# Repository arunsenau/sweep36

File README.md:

# Name

sweep36

A 36 key version of the sweep, maintaining the original diodeless pcb.

# Variations

## sweeeeep

why the name sweeeeep? because an elite-c is required to support the extra features, and an elite-c has 5 additional pins... so 5 Es for the 5 extra pins. Yes, it's dumb, I know.

### Descripiton

This is a reversible pcb that is wired only, has per key leds (only on one of the two variations), oled, and choc spacing. In order to continue to support a no diode setup, I added support for the elite-c, and this is now required for the build. You can use alternative elite-c compatible controllers.

### Versions and features

There are 6 versions of this pcb, as found in the pcb/wired-rgb directory:
* choc: No hotswap, 36 keys
* choc-rotated-inner-thumb: No hotswap, 36 keys, rotated inner thumb similar to the corne
* choc-hotswap: Hotswap only, 36 keys
* ks27-choc: Support for both choc and gateron ks-27 switches, no hotswap. Note that ks-27 switches use MX keycaps on a low profile switch. Given it's choc spacing, you will likely need to use custom smaller MX keycaps if using these switches
* choc-evq-inside: No hotswap, 34 key, with an evqwgd001 roller encoder on the inside thumb key
* choc-evq-outside: No hotswap, 34 key, with an evqwgd001 roller encoder on the outside thumb key

## swweeep

So, to keep the silliness going, this is has an extra W for the wireless only, and 3 Es for the 3 extra required pins on the nice!nano.

### Description (and story)

This was created after the sweeeeep as a wireless alternative. Given the nice!nano has two less gpio than the elite-c, had to remove the data pin (and therefore TRRS). So, this is wireless only!

Given it's a wireless only build, it made sense to add nice!view support, given it consumes 1000x less power than the typical OLED. That meant that it would consume one too many gpio. In the spirit of low power consumption, removing per key rgb was a natural decision, leaving it with just enough gpio for this board.

So, backstory aside, the net of it is:
* nice!nano required
* nice!view support
* wireless only (no TRRS)
* JST spaced battery through holes
* on/off switch
* both kailh hotswap and mill max compatible through hole

Special thanks to @jasonhazel for kickstarting the initiative!

### Notes

Regarding the JST footprint, you can solder directly or use jst. If soldering, connect power to the middle hole (with the +) and GND to the -. If using JST, be sure to look at your battery wiring and connect the JST connector such that the power lines up with the middle pin (again, with thhe + on the silkscreen)

It is possible to also produce a PCB baseplate board for the swweeep with a nice silkscreen, the kicad files are [here](https://github.com/sadekbaroudi/sweep36/tree/master/sweeeeep), or if you think the [Great Wave Off Kanagawa](https://en.wikipedia.org/wiki/The_Great_Wave_off_Kanagawa) would make a good silkscreen, the gerbers for that are [here](https://github.com/sadekbaroudi/sweep36/blob/master/swweeep/swweeep-base/gerber/v1.0-kanagawa-gerbers.zip)

## dweeeeep

### Description

This was created after both of the other variations. It was created as an alternative to the sweeeeep. It's a sweeeeep with diodes. I know the principle of the original sweep was to have no diodes. I apologize, this was a special request to allow people to use a pro micro compatible controller, as they're much cheaper.

# Support me!

I have spent a lot of time and money designing prototypes, testing, developing, etc. Any contributions would be greatly appreciated!

If you don't want to, or can't afford to support me, please send me a message to let me know you've built one, along with pictures. Also, feel free to submit a pull request with pictures into this repository. I'd be happy to showcase your build.

Reddit: /u/sadekbaroudi
Discord: sadekbaroudi#1258

# Firmware

## Vial (wired version only)

Special thanks to [Jason Hazel](https://github.com/jasonhazel) for adding vial support. Note that given vial with split code takes up most of the space, there is no support for the OLED or per key RGB. If you want those features, please use QMK below.

https://github.com/sadekbaroudi/vial-qmk/tree/vial/keyboards/fingerpunch/sweeeeep

## QMK (wired version only)

https://github.com/sadekbaroudi/qmk_firmware/tree/master/keyboards/fingerpunch/sweeeeep

## ZMK (wireless version only)

https://github.com/sadekbaroudi/zmk-fingerpunch-keyboards

# swweeep v1.3 fix

If you built a swweeep v1.3 or earlier, you will need to connect the battery ground pin to the controller gnd pin, as shown below:

# Pictures

## swweeep with nice!view

## swweeep with the base plate

## sweeeeep choc

## sweeeeep evq inside

### sweeeeep (choc)
| Front | Back |
| :---: | :---: |
|  |  |

### sweeeeep (choc-evq-inside)
| Front | Back |
| :---: | :---: |
|  |  |

### sweeeeep (choc-evq-outside)
| Front | Back |
| :---: | :---: |
|  |  |

### sweeeeep (choc-hotswap)
| Front | Back |
| :---: | :---: |
|  |  |

### sweeeeep (choc-rotated-inner-thumb)
| Front | Back |
| :---: | :---: |
|  |  |

### sweeeeep (ks27-choc)
| Front | Back |
| :---: | :---: |
|  |  |

### swweeep (choc-hotswap-optional)
| Front | Back |
| :---: | :---: |
|  |  |

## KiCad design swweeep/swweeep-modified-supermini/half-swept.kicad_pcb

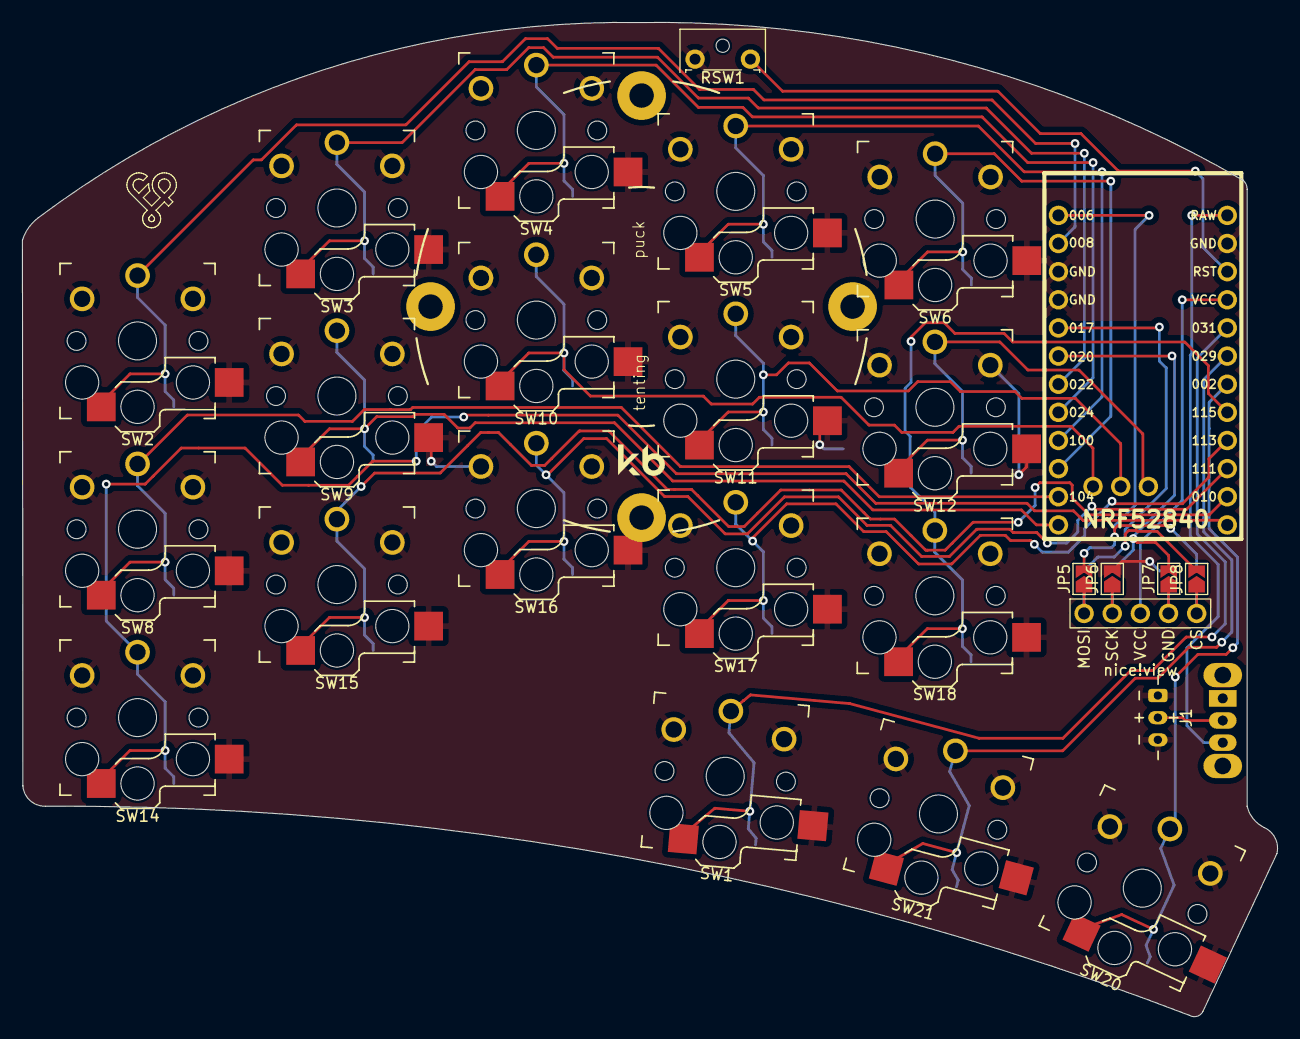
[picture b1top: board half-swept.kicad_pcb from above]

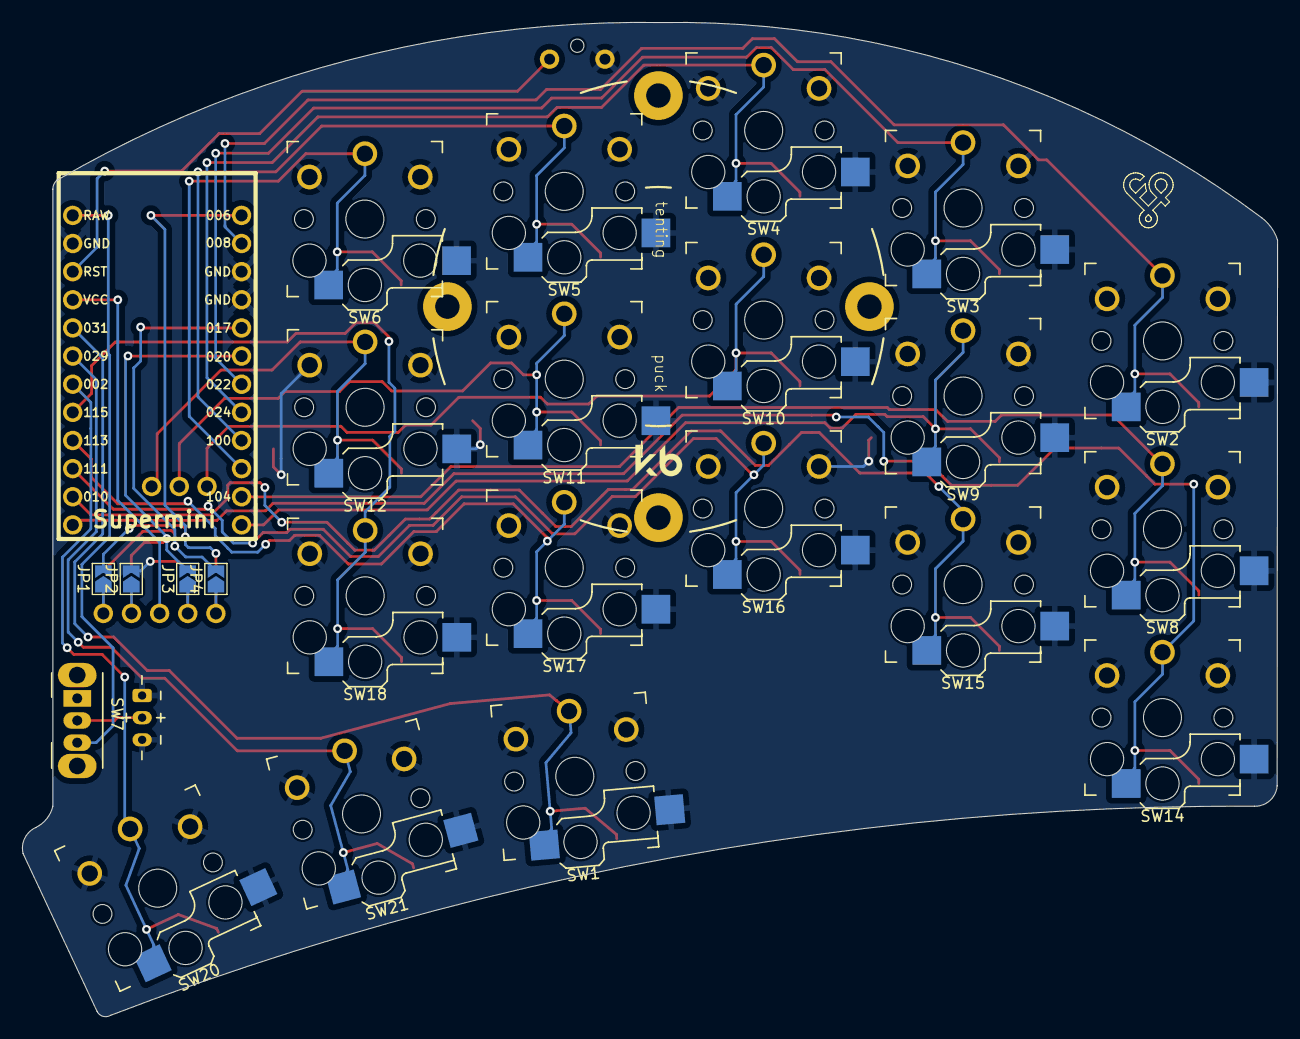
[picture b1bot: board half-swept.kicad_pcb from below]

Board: 2 copper layers, 113.3 x 89.7 mm, 31 parts (5 on the bottom side), 30 nets.

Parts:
Display1: nice!view; nice_view
J1: JST-BATTERY; JST_PH_S3B-PH-K-keyboard
JP1, JP2, JP3, JP4, JP5, JP6, JP7, JP8: Jumper_2_Open; SolderJumper-2_P1.3mm_Open_TrianglePad1.0x1.5mm
RSW1: SW_Push; SW_Tactile_SPST_Angled_MJTP1117-no-mount
SW1, SW2, SW3, SW4, SW5, SW6, SW8, SW9, SW10, SW11, SW12, SW14, SW15, SW16, SW17, SW18, SW20, SW21: SW_Push; Kailh_socket_PG1350_optional_reversible_millmax
SW7: SW_DPDT; SW_CuK_OS102011MA1QN1_SPDT_Angled
U1: nice_nano

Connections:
unnamed: Display1.1 (MOSI), JP4.1 (A), JP5.1 (A)
unnamed: Display1.2 (SCK), JP3.1 (A), JP6.1 (A)
unnamed: Display1.4 (GND), JP2.1 (A), JP7.1 (A)
unnamed: Display1.5 (CS), JP1.1 (A), JP8.1 (A)
unnamed: J1.2, SW7.2 (B)
Switch1: SW2.1, U1.2 (RX1/P0.08)
Switch2: SW3.1, U1.7 (P0.22)
Switch3: SW4.1, U1.8 (P0.24)
Switch4: SW5.1, U1.9 (P1.00)
Switch5: SW6.1, U1.10 (P0.11)
Switch6: SW8.1, U1.11 (P1.04)
Switch7: SW9.1, U1.12 (P1.06)
Switch8: SW10.1, U1.31 (P1.01)
Switch9: SW11.1, U1.32 (P1.02)
Switch10: SW12.1, U1.33 (P1.07)
Switch11: SW14.1, U1.13 (NFC1/P0.09)
Switch12: SW15.1, U1.14 (NFC2/P0.10)
Switch13: SW16.1, U1.15 (P1.11)
Switch14: SW17.1, U1.16 (P1.13)
Switch15: SW18.1, U1.17 (P1.15)
Switch16: SW20.1, U1.18 (AIN0/P0.02)
Switch17: SW21.1, U1.19 (AIN5/P0.29)
Switch18: SW1.1, U1.20 (AIN7/P0.31)
gnd: J1.1, J1.3, JP2.2 (B), JP6.2 (B), RSW1.1, SW1.2, SW2.2, SW3.2, SW4.2, SW5.2, SW6.2, SW8.2, SW9.2, SW10.2, SW11.2, SW12.2, SW14.2, SW15.2, SW16.2, SW17.2, SW18.2, SW20.2, SW21.2, U1.3 (GND), U1.4 (GND), U1.23 (GND)
mosi: JP4.2 (B), JP8.2 (B), U1.5 (P0.17)
nv_cs: JP1.2 (B), JP5.2 (B), U1.1 (TX0/P0.06)
raw: SW7.3 (C), U1.24 (BATIN/P0.04)
reset: RSW1.2, U1.22 (RST)
sck: JP3.2 (B), JP7.2 (B), U1.6 (P0.20)
vcc: Display1.3 (VCC), U1.21 (VCC)

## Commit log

2024-06-24 updated readme to point to new zmk fingerpunch keyboards repo for firmware
2024-10-23 Create swweeep-modified-supermini
2024-10-23 Swweeep Choc hotswap PCBs using Supermini
